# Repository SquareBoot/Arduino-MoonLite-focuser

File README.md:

# Arduino-based telescope focuser controller
Simple MoonLite-compatible motorized focuser controller. Thought to be used with INDI.
Doesn't support temperature compensation.
It also supports a non-official MoonLite-style command to change the state of all the
Arduino's digital and PWM pins: in my case I control two dew heaters and a fan to cool the primary mirror.

### MoonLite focuser
I use a Nema 11 motor that moves the focuser knob using a belt.
If you don't have a heavy focuser, also consider using a Nema 8.
A 20 teeth pulley and a 6mm wide 160mm long belt are enough.
Absolute and relative positioning, half and full step switching.

### Pin management
Define the customizable pins in the `CUSTOMIZABLE_PINS` array in the `Config.h` file and
upload the firmware.

#### AstroAllInOne
<a href="https://github.com/SquareBoot/AstroAllInOne">AstroAllInOne</a>
is this firmware's companion INDI driver that allows the end user to
change the state of **every** pin of the board (pay attention! **do not change the
state of the stepper motor driver's pins**). Refer to its documentation on
how to configure it. Without AstroAllInOne, the Arduino will behave just like
a generic MoonLite focuser controller.

### Polar finder illuminator
For my EQ5 I needed an illuminator and I added it to the focuser project.
It requires a potentiometer to dim the light and a red LED.
Can be easily disabled in the `Config.h` file by setting the `ENABLE_POLAR_LIGHT` field.

### Autodesk Eagle project
In the "Eagle" directory you can find the full circuit project, both schematics and PCB. 
It's the one I use for my telescope, but feel free to modify it to 
accomplish your necessities: for instance, you could add another dew heater controller, 
or remove the Newton mirror cooler MOSFET.
<br>**Made with Eagle 9.2.2 Premium**
<br>

### Mounting brackets
I included the mounting brackets I made for the common SkyWatcher 
dual-speed Crayford focuser (I have a 200mm f/5 Newton OTA).

**AutoCAD 2019** project, STL and IGS exported files.

### Forking & issues
Feel free to submit pull requests! New brackets are welcome!

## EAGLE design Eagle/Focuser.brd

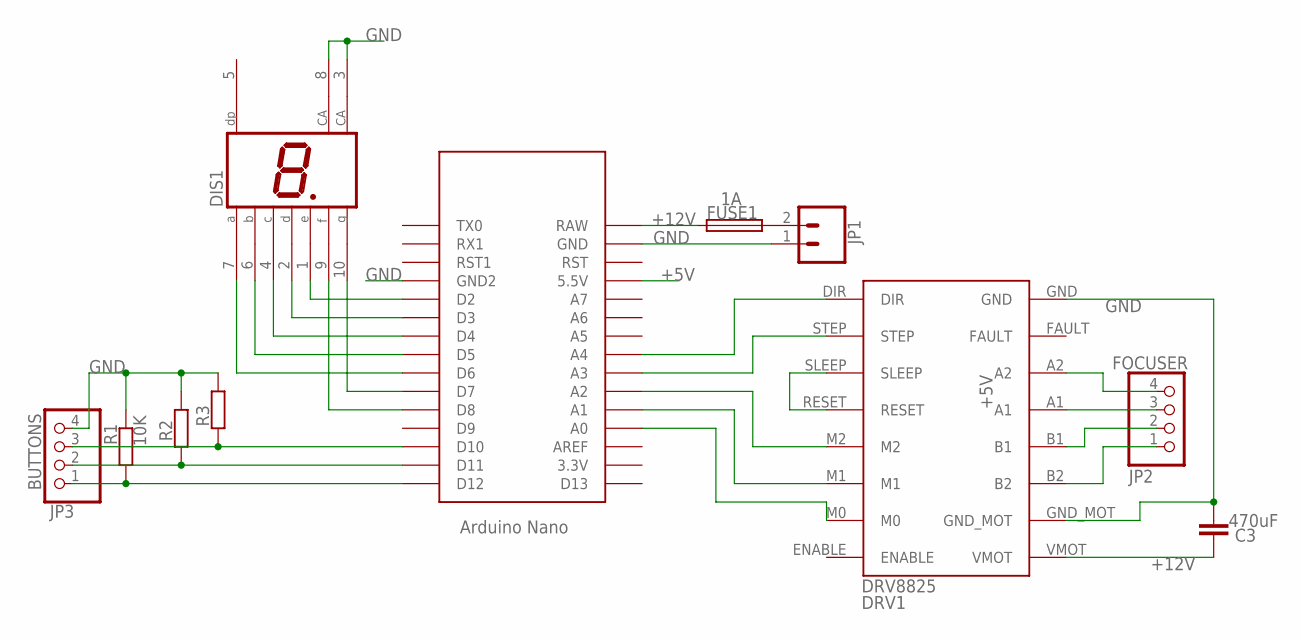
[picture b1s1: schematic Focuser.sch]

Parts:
C3: 470uF; C5B2.5
DIS1: HD-H101; HDSP-M
DRV1: DRV8825
FUSE1: 1A; FUSE_HOLDER_5X20MM
JP1: CONN_025MM; SCREWTERMINAL-5MM-2
JP2: FOCUSER; 1X04
JP3: BUTTONS; 1X04
R1, R2, R3: 10K; 0204V
U$1: NANO

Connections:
+5V: DRV1.RESET, DRV1.SLEEP, U$1.5V (5.5V)
+12V: C3.2, DRV1.VMOT, FUSE1.2, U$1.RAW
GND: C3.1, DIS1.3 (CA), DIS1.8 (CA), DRV1.GND, DRV1.GND_MOT, JP1.1, JP3.4, R1.2, R2.2, R3.2, U$1.GND, U$1.GND1 (GND2)
unnamed: DIS1.1 (E), U$1.D2
unnamed: JP3.3, R3.1, U$1.D10
unnamed: JP3.2, R2.1, U$1.D11
unnamed: JP3.1, R1.1, U$1.D12
unnamed: DRV1.DIR, U$1.A4
unnamed: DIS1.2 (D), U$1.D3
unnamed: FUSE1.1, JP1.2
unnamed: DIS1.4 (C), U$1.D4
unnamed: DIS1.6 (B), U$1.D5
unnamed: DIS1.7 (A), U$1.D6
unnamed: DIS1.10 (G), U$1.D7
unnamed: DRV1.STEP, U$1.A3
unnamed: DRV1.B2, JP2.1
unnamed: DRV1.B1, JP2.2
unnamed: DRV1.A1, JP2.3
unnamed: DRV1.A2, JP2.4
unnamed: DRV1.M2, U$1.A2
unnamed: DRV1.M1, U$1.A1
unnamed: DIS1.9 (F), U$1.D8
unnamed: DRV1.M0, U$1.A0

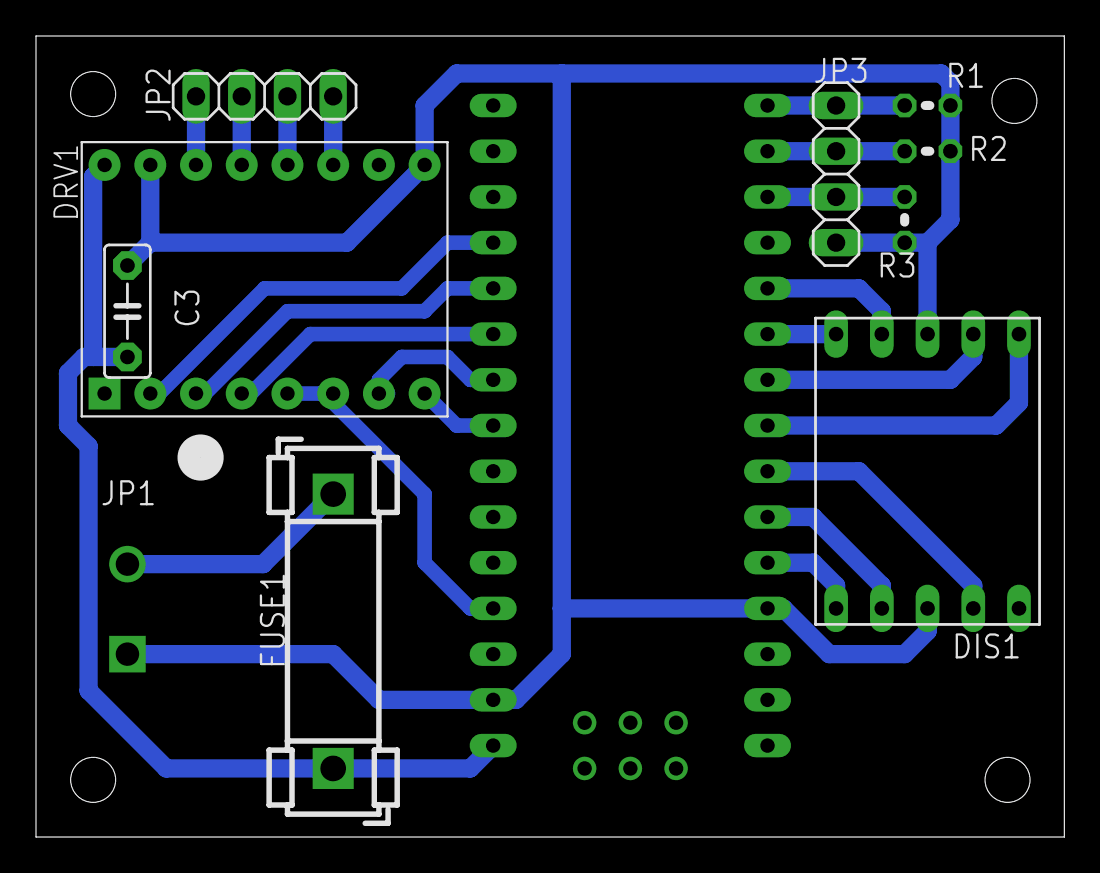
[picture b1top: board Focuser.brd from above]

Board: 2 copper layers, 57.1 x 44.5 mm, 11 parts (1 on the bottom side), 23 nets.

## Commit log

2018-11-01 Better brackets
2018-11-01 Circuit for commercial version
2018-11-02 Hand control added in circuit
2018-11-02 HC support in firmware
2018-11-02 Backlight cmd

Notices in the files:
parts and their libraries:
SparkFun-Connectors: Licensing: Creative Commons ShareAlike 4.0 International - https://creativecommons.org/licenses/by-sa/4.0
